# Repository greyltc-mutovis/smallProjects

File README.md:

# smallProjects

Random bits of various things.

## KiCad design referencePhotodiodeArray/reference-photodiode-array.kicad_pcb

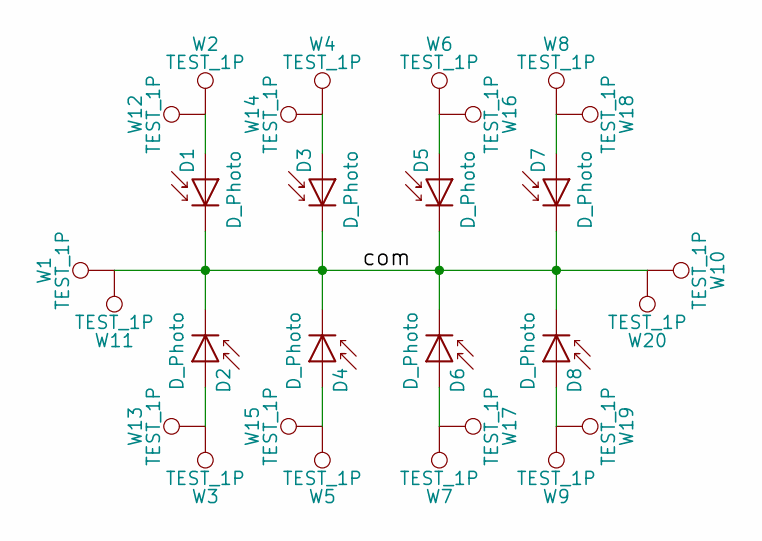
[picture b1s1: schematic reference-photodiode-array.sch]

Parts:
D1, D2, D3, D4, D5, D6, D7, D8: D_Photo; BPW34
W1, W2, W3, W4, W5, W6, W7, W8, W9, W10, W11, W12, W13, W14, W15, W16, W17, W18, W19, W20: TEST_1P; SolderWirePad_single_SMD_5x2.3mm

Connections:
/com: D1.1 (K), D2.1 (K), D3.1 (K), D4.1 (K), D5.1 (K), D6.1 (K), D7.1 (K), D8.1 (K), W1.1, W10.1, W11.1, W20.1
unnamed: D1.2 (A), W2.1, W12.1
unnamed: D2.2 (A), W3.1, W13.1
unnamed: D3.2 (A), W4.1, W14.1
unnamed: D4.2 (A), W5.1, W15.1
unnamed: D5.2 (A), W6.1, W16.1
unnamed: D6.2 (A), W7.1, W17.1
unnamed: D7.2 (A), W8.1, W18.1
unnamed: D8.2 (A), W9.1, W19.1

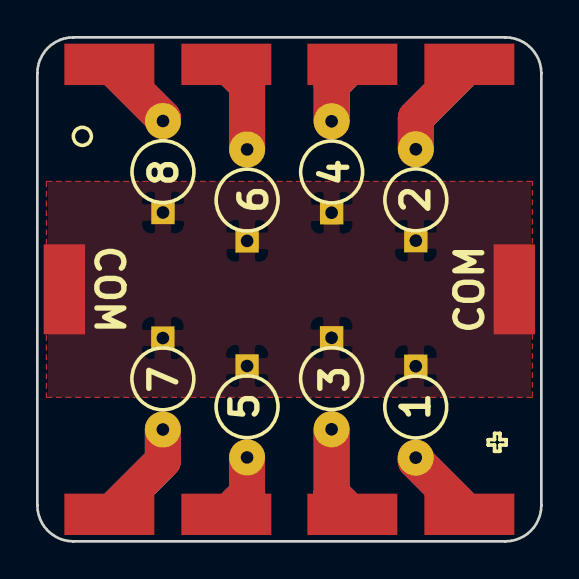
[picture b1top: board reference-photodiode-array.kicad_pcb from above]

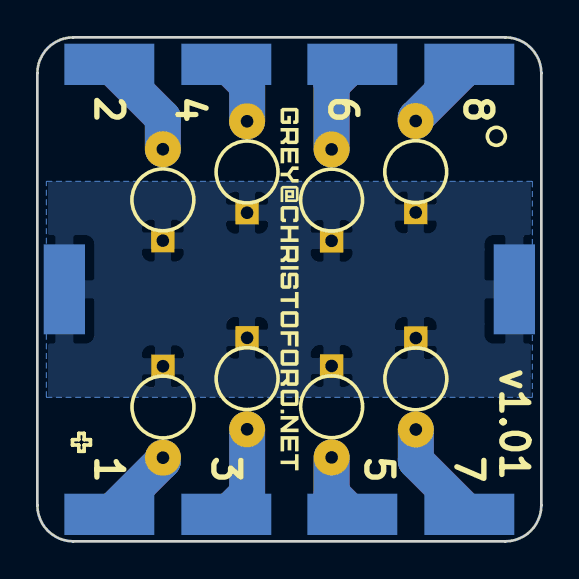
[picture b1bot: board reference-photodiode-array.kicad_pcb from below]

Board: 2 copper layers, 28.0 x 28.0 mm, 28 parts (18 on the bottom side), 9 nets.

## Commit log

2015-10-13 added main body for giles substrate holder
2015-10-13 clips both sides now, dual purpose with ribbon opening
2015-10-13 triangle holes
2015-10-13 add gcode
2015-10-13 proper triangle holes
2015-10-13 square holes with support during print
2015-10-13 1 mm taller
2015-10-18 added cap
2015-10-18 add cap stl and gcode
2015-10-19 tweaks to cap
2015-10-19 add tabs for binder clips, widen legs and shelf
2015-10-19 move a few variables around
2015-10-20 adjust tolerances
2015-10-20 clean up: add comments, add cap tolerance
2015-10-20 update .gcode files
2015-11-11 new stl and gcode for cap
2015-11-20 add offset with cap
2015-11-20 add offset cap gcode
2015-12-18 add encapsulation tool
2015-12-18 move scad
2016-01-27 b40 bell and top flange model done
2016-01-27 update to importing ezfreecad
2016-01-27 b40 model finished
2016-01-28 add evap plane and motor model
2016-01-28 shift motor
2016-01-28 add carousel
2016-01-28 try adding webgl
2016-02-05 b40 workings
2016-02-05 first piece of bracket done
2016-02-05 working on bracket
2016-02-07 carousel done
2016-02-13 v2.0 of mask wheel
2016-03-01 Create LICENSE
2016-05-22 remove editor
2016-05-22 b40 was moved to a new repo
2016-07-20 Adding .stl file for basket holder
2016-07-23 Adding drawings of holder for tandem
2016-07-23 adding gcode files
2016-07-24 Added lids and screws holes on cell holders
2016-07-30 adjusted tollerances on mirror holders
2016-10-21 reduce height because new pins are way shorter - regenerate .stl files for four point probe holder
2016-10-21 add new gcode files for 4pp substrate holder
2016-10-23 major upgrades: key slot to prevent misalignment substrate alignment marks cable retention new wing design pcb mounting holes
2016-10-23 take vacancies page from internal wiki
2016-10-28 add nozzle insert drawing
2016-10-28 fix dims for threads
2016-10-31 move around some dims
2016-10-31 added milling folder
2016-10-31 update holder
2016-10-31 add shipped grbl frimware for shapeoko3 (version 0.9g)
2016-10-31 update with some firmware instructions
2016-10-31 add note to hold cap
2016-10-31 add latest grbl 0.9j firmware
2016-10-31 Add enable homing
2016-10-31 add carbide connect settings
2016-11-01 add proper grbl settings for firmware ver 0.9j
2016-11-01 add some adapter design files
2016-11-02 ready to cut
2016-11-13 working on test structures in Al
2016-12-03 add holder image
2016-12-03 add image to readme
2016-12-14 add slice readme
2016-12-15 formatting
2016-12-15 explode slices
2016-12-15 slices in one file
2016-12-20 trying out bCNC workflow
2016-12-21 fix up shoe with freecad
2016-12-21 fixed up stp, regenerated stl, redraw of dxf to focus on planes, generated toolpaths.
2017-01-21 add some shapoko stuff
2017-01-21 add complex optimization/fitting example
2017-01-21 Correct model
2017-01-22 add evaluation plot
2017-01-22 github fails at .svg
2017-01-22 link to graph
2017-01-22 added some matlab
2017-01-28 add pro toolpath from fusion 360
2017-01-28 add fusion 360 instructions
2017-02-02 add 2d shoe
2017-02-04 move dust shoe layers
2017-02-04 made step for new shoe
2017-02-04 made part 20 --> 19mm thick
2017-02-04 made path for shoe mount
2017-02-09 added photodiode array pcb
2017-02-10 diode substrate design "done"
2017-02-20 dd 30x30 holder
2017-02-25 update small projects
2017-02-28 this is the config.h provided by carbide3d for building their firmware
    http://community.carbide3d.com/t/grbl-1-1-changes-from-stock/4559/2
2017-02-28 grbl compile and new firmware flash instructions
2017-03-01 fix reference photodiode array
2017-03-01 minor edit
2017-03-01 fixed compile config changes
2017-03-05 Adding gcode for ultimaker
2017-03-06 Added tolerances
2017-03-13 put pads on both sides
2017-06-22 add analog circuit simulation for pules from photodiode
2017-06-22 add two BNC dxf
2017-06-23 new filter setup
2017-07-18 initial commit: modified version of singleSubstrateHolder for IPCE setup
2017-07-18 created 2d projection for measurement and fixed notch offset
2017-07-20 updated distance to focal plane and diameter of photodiode leg holes
2017-07-20 wrapped scripts for parts in modules to make it easy to show projections
2017-07-20 created 2d projections
2017-07-20 updated notch width on photodiode attachment to account for tolerance. Added substrate cavity to position check.
2017-07-20 added substrate layout
2017-07-20 checked 2d layout, updated .stl's
2017-07-21 added x positions of diodes and pixels
2017-08-22 added notes
2017-08-22 add 28x28 single holder with cap also for 30x30
2017-08-23 exported as AutoCAD R14
2017-08-23 exported as svg
2017-08-23 .dwg
2017-09-22 intital openscad designs
2017-09-22 updated sizes
2017-09-28 updated parameters
2017-10-05 updated parameters for o-ring
2017-10-05 updated oring parameters again, created .step files
2017-12-08 3d printed solar sim sample holder
2017-12-14 cap and base for new ss holder v1 done
2017-12-17 device holder cap & clips
2018-01-10 pmt holder work
2018-05-03 made clips slightly shorter, added 25x25
2018-05-04 new 3x3 system, slightly shorter clips
2018-05-04 update 28 system
2018-07-13 design a post extender for the solar sim
2018-07-13 upgrade post extender
2018-08-09 add DFS mounting script
2018-10-17 fix mount script, fix solar sim post extender, add glass scratcher design
